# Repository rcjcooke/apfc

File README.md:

# apfc
Aeroponics Personal Food Computer

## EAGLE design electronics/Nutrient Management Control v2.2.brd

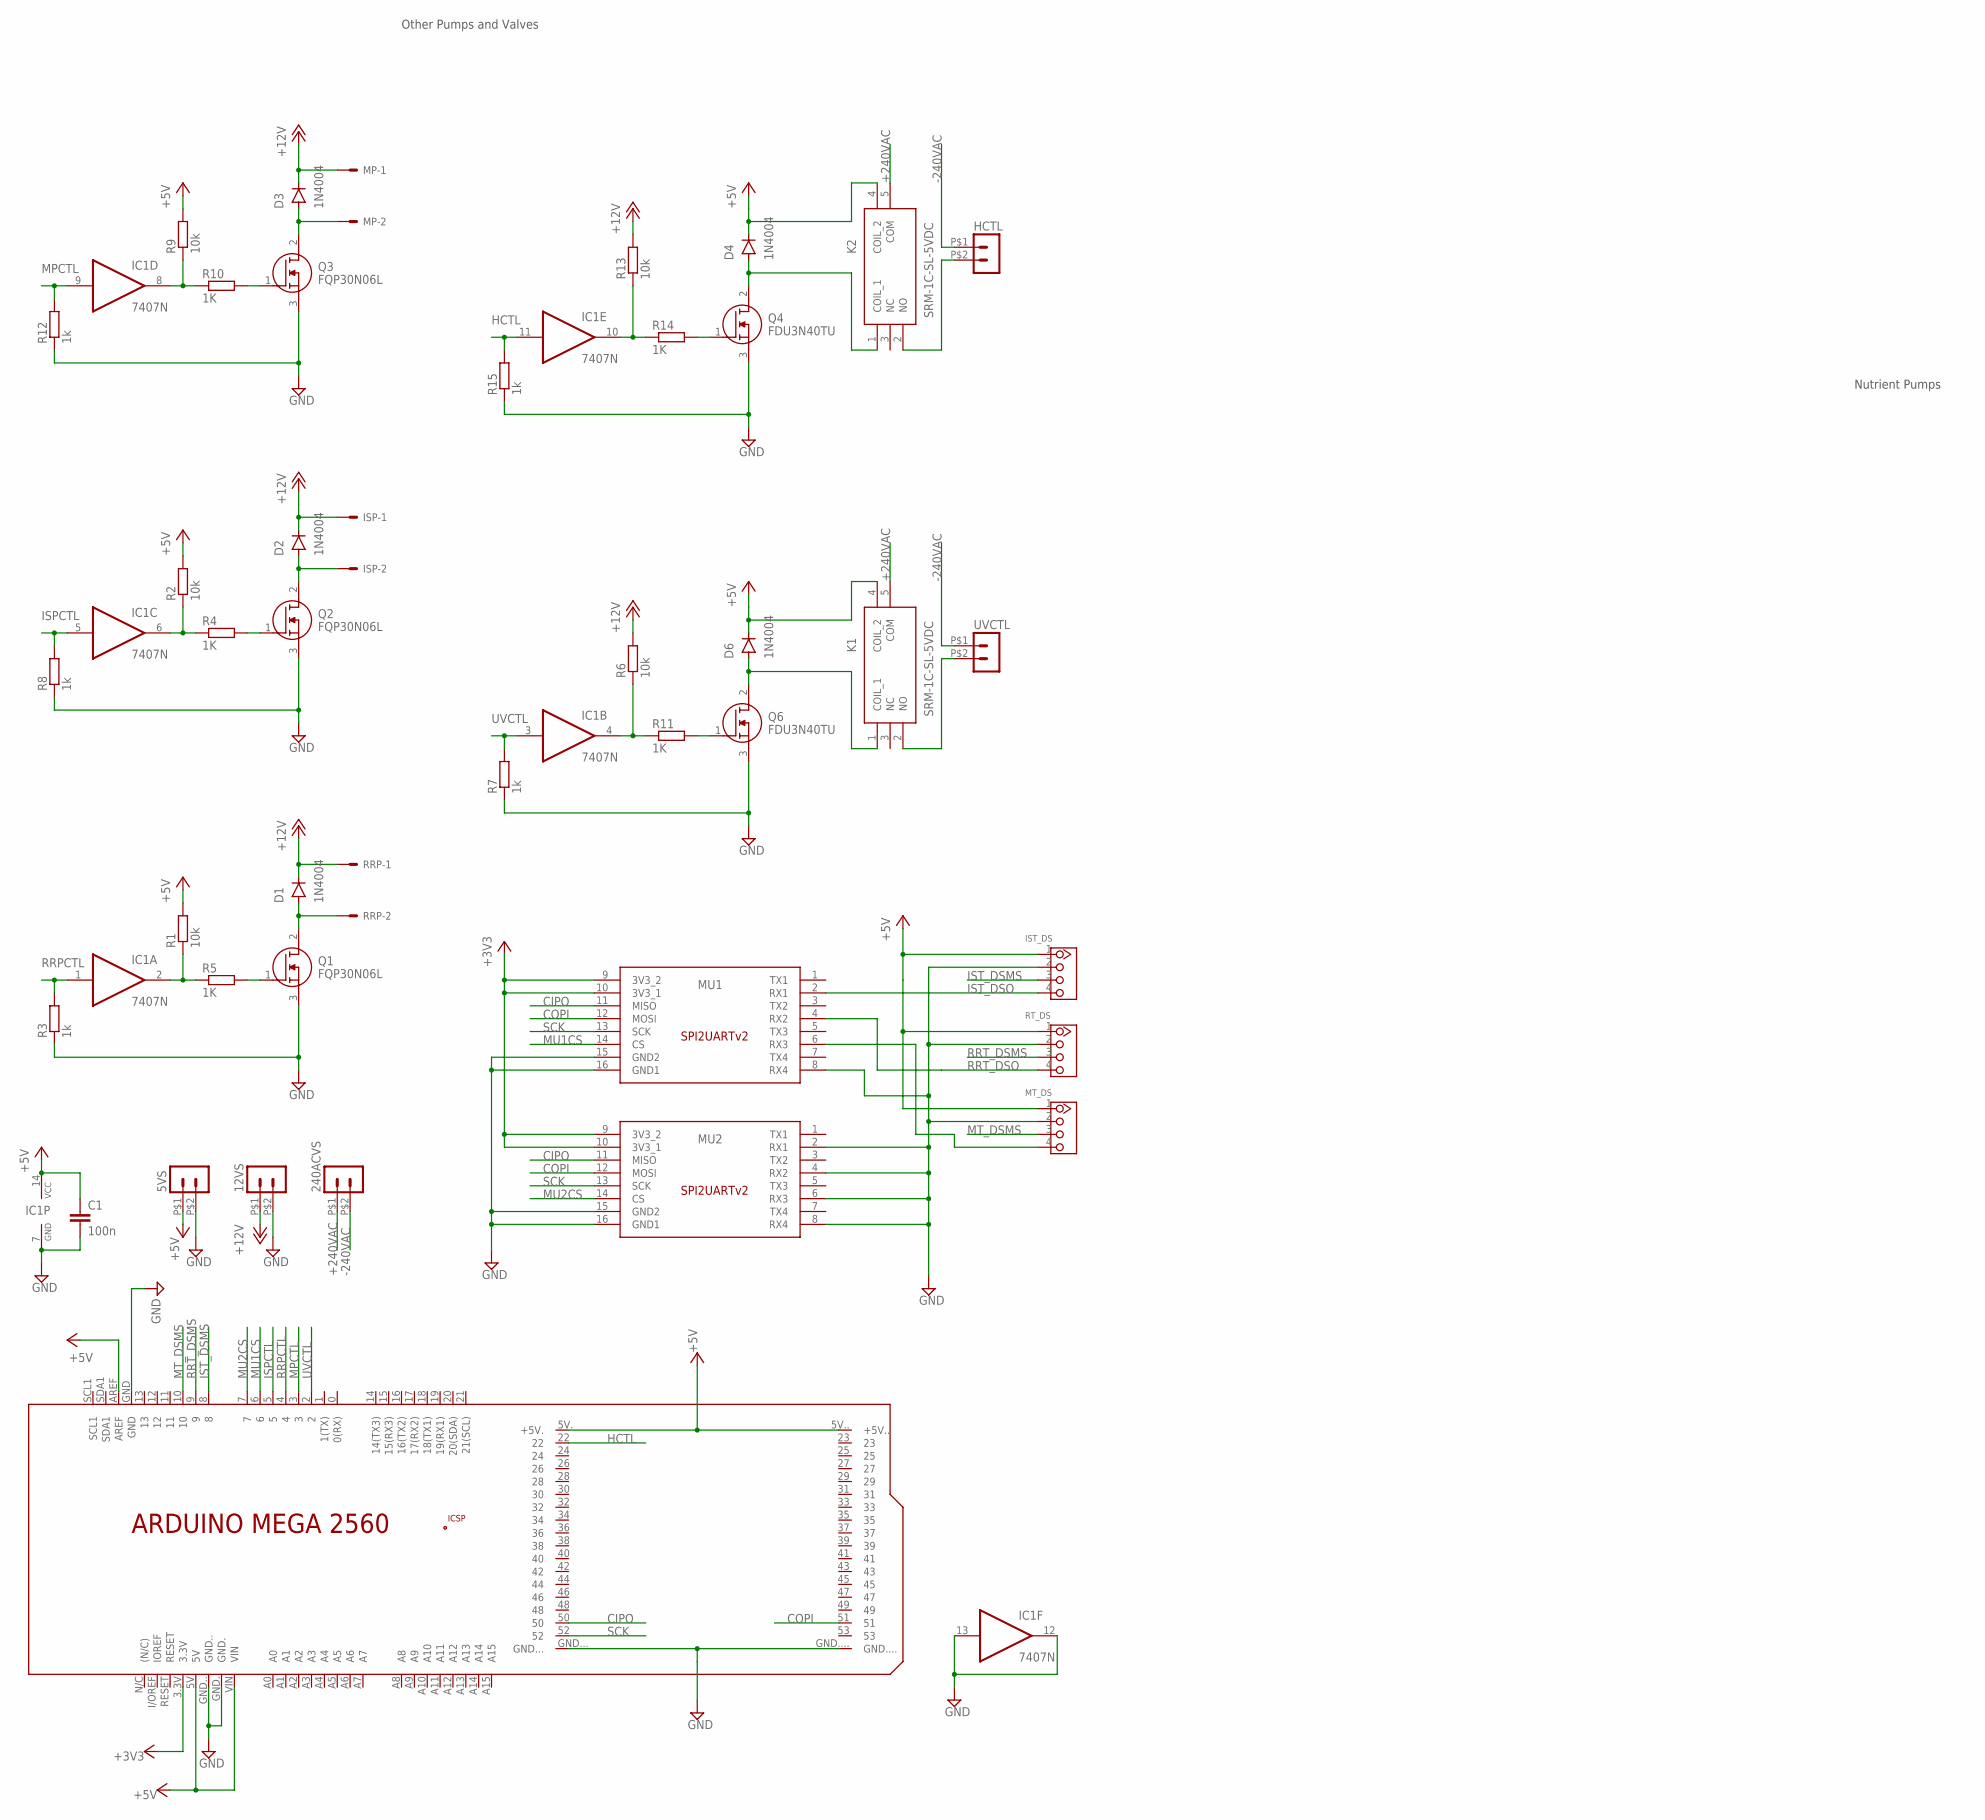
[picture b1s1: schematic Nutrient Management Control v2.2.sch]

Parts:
5VS, 12VS, 240ACVS: HEADER_POS2_43650-0215; 43650-0215
C1: 100n; C050-024X044
D1, D2, D3, D4, D6: 1N4004; DO-41
HCTL: HEADER_POS2_43650-0215; 43650-0215
IC1: 7407N; DIL14
ISP: JST-XH-02-PIN-LONG-PAD; JST-XH-02-PACKAGE-LONG-PAD
IST_DS: 4P-2.0-90D; HW4-2.0-90D
K1, K2: SRM-1C-SL-5VDC; SRM1CSL5VDC
MP: JST-XH-02-PIN-LONG-PAD; JST-XH-02-PACKAGE-LONG-PAD
MT_DS: 4P-2.0-90D; HW4-2.0-90D
MU1, MU2: SPI2UART_HEADERS; SPI2UARTV2
PCB2: ARDUINO_MEGA2560_SHIELD
Q1, Q2, Q3: FQP30N06L; TO254P470X1016X2019-3P
Q4, Q6: FDU3N40TU; TO229P250X658X985-3P
R1, R2, R6, R9, R13: 10k; 0204/7
R3, R7, R8, R12, R15: 1k; 0204/7
R4, R5, R10, R11, R14: 1K; 0204/7
RRP: JST-XH-02-PIN-LONG-PAD; JST-XH-02-PACKAGE-LONG-PAD
RT_DS: 4P-2.0-90D; HW4-2.0-90D
UVCTL: HEADER_POS2_43650-0215; 43650-0215

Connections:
+3V3: MU1.9 (3V3_2), MU1.10 (3V3_1), MU2.9 (3V3_2), MU2.10 (3V3_1), PCB2.3.3V
+5V: 5VS.P$1 (1), C1.1, D4.C, D6.C, IC1.14 (VCC), IST_DS.1, K1.4 (COIL_2), K2.4 (COIL_2), MT_DS.1, PCB2.5V, PCB2.5V. (+5V.), PCB2.5V.. (+5V..), PCB2.AREF, PCB2.VIN, R1.2, R2.2, R9.2, RT_DS.1
+12V: 12VS.P$1 (1), D1.C, D2.C, D3.C, ISP.1, MP.1, R6.2, R13.2, RRP.1
+240VAC: 240ACVS.P$1 (1), K1.5 (COM), K2.5 (COM)
-240VAC: 240ACVS.P$2 (2), HCTL.P$1 (1), UVCTL.P$1 (1)
CIPO: MU1.11 (MISO), MU2.11 (MISO), PCB2.50
COPI: MU1.12 (MOSI), MU2.12 (MOSI), PCB2.51
GND: 5VS.P$2 (2), 12VS.P$2 (2), C1.2, IC1.7 (GND), IC1.12 (O), IC1.13 (I), IST_DS.2, MT_DS.2, MU1.8 (RX4), MU1.15 (GND2), MU1.16 (GND1), MU2.2 (RX1), MU2.4 (RX2), MU2.6 (RX3), MU2.8 (RX4), MU2.15 (GND2), MU2.16 (GND1), PCB2.GND, PCB2.GND., PCB2.GND.., PCB2.GND..., PCB2.GND...., Q1.3 (S), Q2.3 (S), Q3.3 (S), Q4.3 (S), Q6.3 (S), R3.1, R7.1, R8.1, R12.1, R15.1, RT_DS.2
HCTL: IC1.11 (I), PCB2.22, R15.2
ISPCTL: IC1.5 (I), PCB2.5, R8.2
IST_DSMS: IST_DS.3, PCB2.8
IST_DSO: IST_DS.4, MU1.2 (RX1)
MPCTL: IC1.9 (I), PCB2.3, R12.2
MT_DSMS: MT_DS.3, PCB2.10
MU1CS: MU1.14 (CS), PCB2.6
MU2CS: MU2.14 (CS), PCB2.7
unnamed: D2.A, ISP.2, Q2.2 (D)
unnamed: IC1.6 (O), R2.1, R4.1
unnamed: IC1.2 (O), R1.1, R5.1
unnamed: Q2.1 (G), R4.2
unnamed: Q1.1 (G), R5.2
unnamed: D3.A, MP.2, Q3.2 (D)
unnamed: K1.2 (NO), UVCTL.P$2 (2)
unnamed: IC1.8 (O), R9.1, R10.1
unnamed: Q3.1 (G), R10.2
unnamed: D1.A, Q1.2 (D), RRP.2
unnamed: MT_DS.4, MU1.6 (RX3)
unnamed: D4.A, K2.1 (COIL_1), Q4.2 (D)
unnamed: Q6.1 (G), R11.2
unnamed: HCTL.P$2 (2), K2.2 (NO)
unnamed: Q4.1 (G), R14.2
unnamed: IC1.10 (O), R13.1, R14.1
unnamed: IC1.4 (O), R6.1, R11.1
unnamed: D6.A, K1.1 (COIL_1), Q6.2 (D)
RRPCTL: IC1.1 (I), PCB2.4, R3.2
RRT_DSMS: PCB2.9, RT_DS.3
RRT_DSO: MU1.4 (RX2), RT_DS.4
SCK: MU1.13 (SCK), MU2.13 (SCK), PCB2.52
UVCTL: IC1.3 (I), PCB2.2, R7.2

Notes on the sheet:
Nutrient Pumps
Other Pumps and Valves

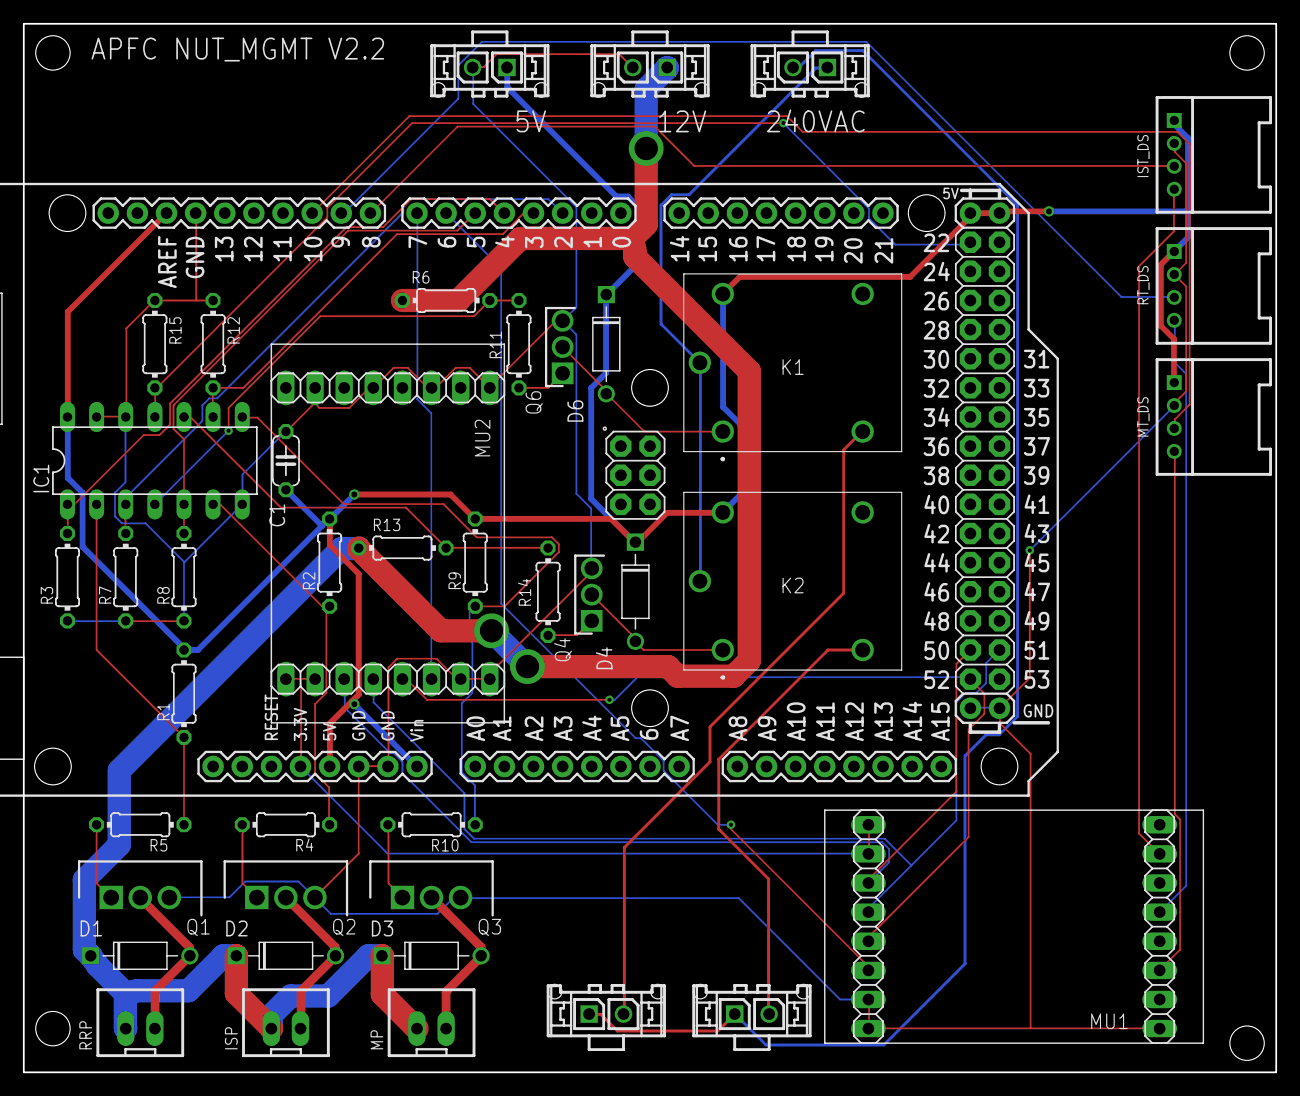
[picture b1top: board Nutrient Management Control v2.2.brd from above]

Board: 2 copper layers, 109.2 x 91.4 mm, 43 parts (0 on the bottom side), 39 nets.

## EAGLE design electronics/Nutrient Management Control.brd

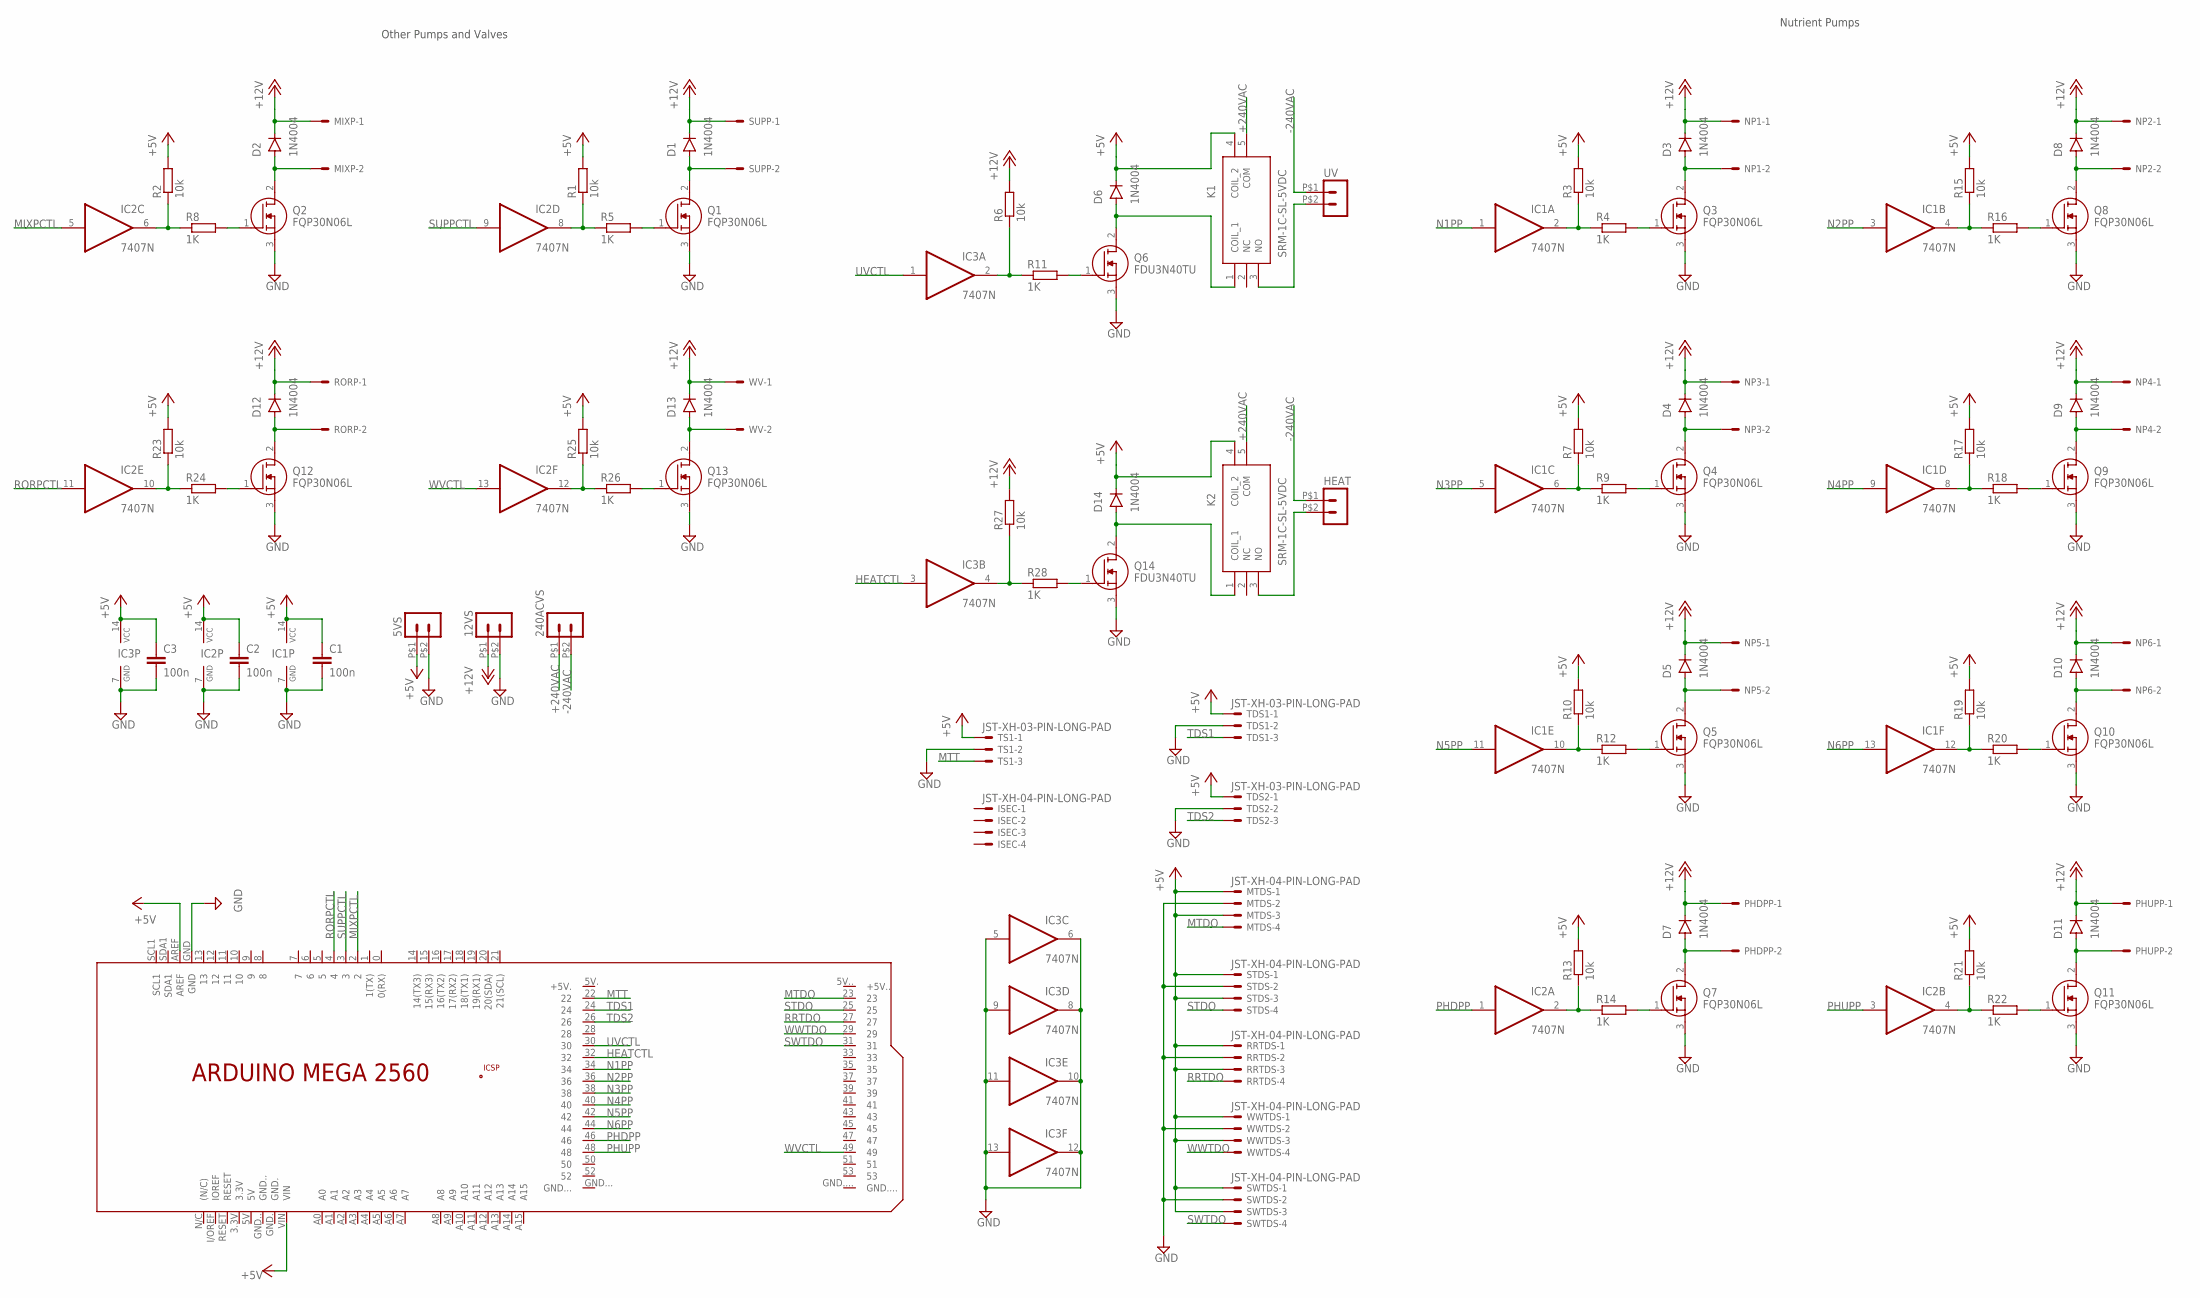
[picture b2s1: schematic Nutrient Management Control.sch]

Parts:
5VS, 12VS, 240ACVS: HEADER_POS2_43650-0215; 43650-0215
C1, C2, C3: 100n; C050-024X044
D1, D2, D3, D4, D5, D6, D7, D8, D9, D10, D11, D12, D13, D14: 1N4004; DO-41
HEAT: HEADER_POS2_43650-0215; 43650-0215
IC1, IC2, IC3: 7407N; DIL14
ISEC: JST-XH-04-PIN-LONG-PAD; JST-XH-04-PACKAGE-LONG-PAD
K1, K2: SRM-1C-SL-5VDC; SRM1CSL5VDC
MIXP: JST-XH-02-PIN-LONG-PAD; JST-XH-02-PACKAGE-LONG-PAD
MTDS: JST-XH-04-PIN-LONG-PAD; JST-XH-04-PACKAGE-LONG-PAD
NP1, NP2, NP3, NP4, NP5, NP6: JST-XH-02-PIN-LONG-PAD; JST-XH-02-PACKAGE-LONG-PAD
PCB2: ARDUINO_MEGA2560_SHIELD
PHDPP: JST-XH-02-PIN-LONG-PAD; JST-XH-02-PACKAGE-LONG-PAD
PHUPP: JST-XH-02-PIN-LONG-PAD; JST-XH-02-PACKAGE-LONG-PAD
Q1, Q2, Q3, Q4, Q5, Q7, Q8, Q9, Q10, Q11, Q12, Q13: FQP30N06L; TO254P470X1016X2019-3P
Q6, Q14: FDU3N40TU; TO229P250X658X985-3P
R1, R2, R3, R6, R7, R10, R13, R15, R17, R19, R21, R23, R25, R27: 10k; 0204/7
R4, R5, R8, R9, R11, R12, R14, R16, R18, R20, R22, R24, R26, R28: 1K; 0204/7
RORP: JST-XH-02-PIN-LONG-PAD; JST-XH-02-PACKAGE-LONG-PAD
RRTDS: JST-XH-04-PIN-LONG-PAD; JST-XH-04-PACKAGE-LONG-PAD
STDS: JST-XH-04-PIN-LONG-PAD; JST-XH-04-PACKAGE-LONG-PAD
SUPP: JST-XH-02-PIN-LONG-PAD; JST-XH-02-PACKAGE-LONG-PAD
SWTDS: JST-XH-04-PIN-LONG-PAD; JST-XH-04-PACKAGE-LONG-PAD
TDS1, TDS2: JST-XH-03-PIN-LONG-PAD; JST-XH-03-PACKAGE-LONG-PAD
TS1: JST-XH-03-PIN-LONG-PAD; JST-XH-03-PACKAGE-LONG-PAD
UV: HEADER_POS2_43650-0215; 43650-0215
WV: JST-XH-02-PIN-LONG-PAD; JST-XH-02-PACKAGE-LONG-PAD
WWTDS: JST-XH-04-PIN-LONG-PAD; JST-XH-04-PACKAGE-LONG-PAD

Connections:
+5V: 5VS.P$1 (1), C1.1, C2.1, C3.1, D6.C, D14.C, IC1.14 (VCC), IC2.14 (VCC), IC3.14 (VCC), K1.4 (COIL_2), K2.4 (COIL_2), MTDS.1, MTDS.3, PCB2.AREF, PCB2.VIN, R1.2, R2.2, R3.2, R7.2, R10.2, R13.2, R15.2, R17.2, R19.2, R21.2, R23.2, R25.2, RRTDS.1, RRTDS.3, STDS.1, STDS.3, SWTDS.1, SWTDS.3, TDS1.1, TDS2.1, TS1.1, WWTDS.1, WWTDS.3
+12V: 12VS.P$1 (1), D1.C, D2.C, D3.C, D4.C, D5.C, D7.C, D8.C, D9.C, D10.C, D11.C, D12.C, D13.C, MIXP.1, NP1.1, NP2.1, NP3.1, NP4.1, NP5.1, NP6.1, PHDPP.1, PHUPP.1, R6.2, R27.2, RORP.1, SUPP.1, WV.1
+240VAC: 240ACVS.P$1 (1), K1.5 (COM), K2.5 (COM)
-240VAC: 240ACVS.P$2 (2), HEAT.P$1 (1), UV.P$1 (1)
GND: 5VS.P$2 (2), 12VS.P$2 (2), C1.2, C2.2, C3.2, IC1.7 (GND), IC2.7 (GND), IC3.5 (I), IC3.6 (O), IC3.7 (GND), IC3.8 (O), IC3.9 (I), IC3.10 (O), IC3.11 (I), IC3.12 (O), IC3.13 (I), MTDS.2, PCB2.GND, Q1.3 (S), Q2.3 (S), Q3.3 (S), Q4.3 (S), Q5.3 (S), Q6.3 (S), Q7.3 (S), Q8.3 (S), Q9.3 (S), Q10.3 (S), Q11.3 (S), Q12.3 (S), Q13.3 (S), Q14.3 (S), RRTDS.2, STDS.2, SWTDS.2, TDS1.2, TDS2.2, TS1.2, WWTDS.2
HEATCTL: IC3.3 (I), PCB2.32
MIXPCTL: IC2.5 (I), PCB2.2
MTDO: MTDS.4, PCB2.23
MTT: PCB2.22, TS1.3
N1PP: IC1.1 (I), PCB2.34
N2PP: IC1.3 (I), PCB2.36
N3PP: IC1.5 (I), PCB2.38
N4PP: IC1.9 (I), PCB2.40
N5PP: IC1.11 (I), PCB2.42
N6PP: IC1.13 (I), PCB2.44
unnamed: D2.A, MIXP.2, Q2.2 (D)
unnamed: D3.A, NP1.2, Q3.2 (D)
unnamed: IC2.8 (O), R1.1, R5.1
unnamed: Q2.1 (G), R8.2
unnamed: Q1.1 (G), R5.2
unnamed: IC1.2 (O), R3.1, R4.1
unnamed: K1.3 (NO), UV.P$2 (2)
unnamed: Q3.1 (G), R4.2
unnamed: IC2.6 (O), R2.1, R8.1
unnamed: D1.A, Q1.2 (D), SUPP.2
unnamed: D4.A, NP3.2, Q4.2 (D)
unnamed: IC1.6 (O), R7.1, R9.1
unnamed: Q6.1 (G), R11.2
unnamed: Q4.1 (G), R9.2
unnamed: D5.A, NP5.2, Q5.2 (D)
unnamed: IC1.10 (O), R10.1, R12.1
unnamed: IC3.2 (O), R6.1, R11.1
unnamed: Q5.1 (G), R12.2
unnamed: D7.A, PHDPP.2, Q7.2 (D)
unnamed: IC2.2 (O), R13.1, R14.1
unnamed: D6.A, K1.1 (COIL_1), Q6.2 (D)
unnamed: Q7.1 (G), R14.2
unnamed: D8.A, NP2.2, Q8.2 (D)
unnamed: IC1.4 (O), R15.1, R16.1
unnamed: Q8.1 (G), R16.2
unnamed: D9.A, NP4.2, Q9.2 (D)
unnamed: IC1.8 (O), R17.1, R18.1
unnamed: Q9.1 (G), R18.2
unnamed: D10.A, NP6.2, Q10.2 (D)
unnamed: IC1.12 (O), R19.1, R20.1
unnamed: Q10.1 (G), R20.2
unnamed: D11.A, PHUPP.2, Q11.2 (D)
unnamed: IC2.4 (O), R21.1, R22.1
unnamed: Q11.1 (G), R22.2
unnamed: D12.A, Q12.2 (D), RORP.2
unnamed: IC2.10 (O), R23.1, R24.1
unnamed: Q12.1 (G), R24.2
unnamed: D13.A, Q13.2 (D), WV.2
unnamed: IC2.12 (O), R25.1, R26.1
unnamed: Q13.1 (G), R26.2
unnamed: D14.A, K2.1 (COIL_1), Q14.2 (D)
unnamed: HEAT.P$2 (2), K2.3 (NO)
unnamed: Q14.1 (G), R28.2
unnamed: IC3.4 (O), R27.1, R28.1
PHDPP: IC2.1 (I), PCB2.46
PHUPP: IC2.3 (I), PCB2.48
RORPCTL: IC2.11 (I), PCB2.4
RRTDO: PCB2.27, RRTDS.4
STDO: PCB2.25, STDS.4
SUPPCTL: IC2.9 (I), PCB2.3
SWTDO: PCB2.31, SWTDS.4
TDS1: PCB2.24, TDS1.3
TDS2: PCB2.26, TDS2.3
UVCTL: IC3.1 (I), PCB2.30
WVCTL: IC2.13 (I), PCB2.49
WWTDO: PCB2.29, WWTDS.4

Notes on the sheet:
Nutrient Pumps
Other Pumps and Valves

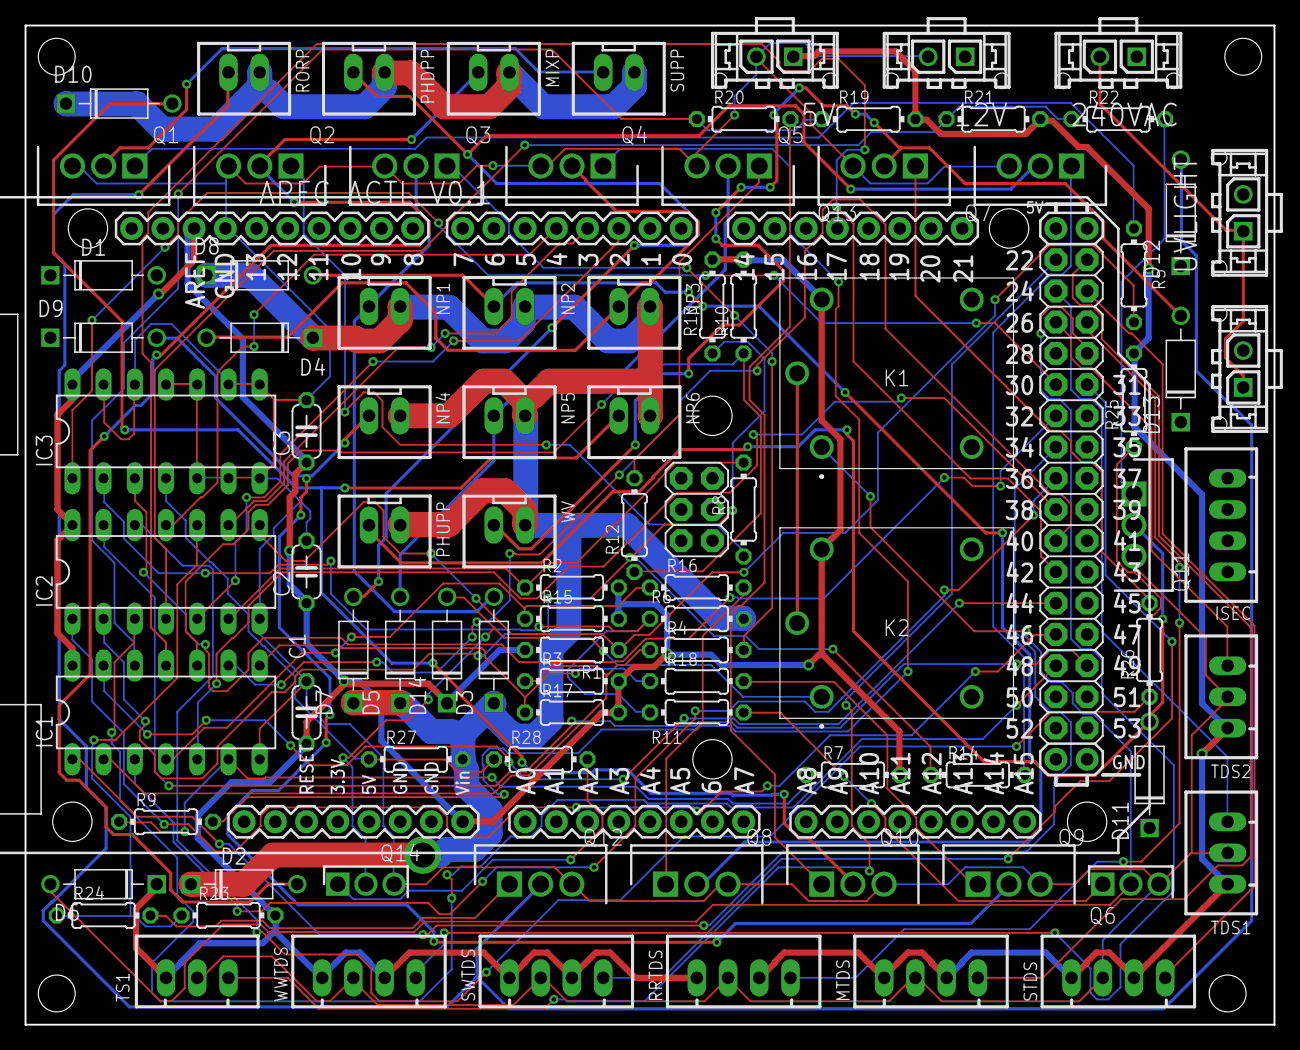
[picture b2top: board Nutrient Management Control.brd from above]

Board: 2 copper layers, 101.6 x 81.3 mm, 91 parts (0 on the bottom side), 71 nets.

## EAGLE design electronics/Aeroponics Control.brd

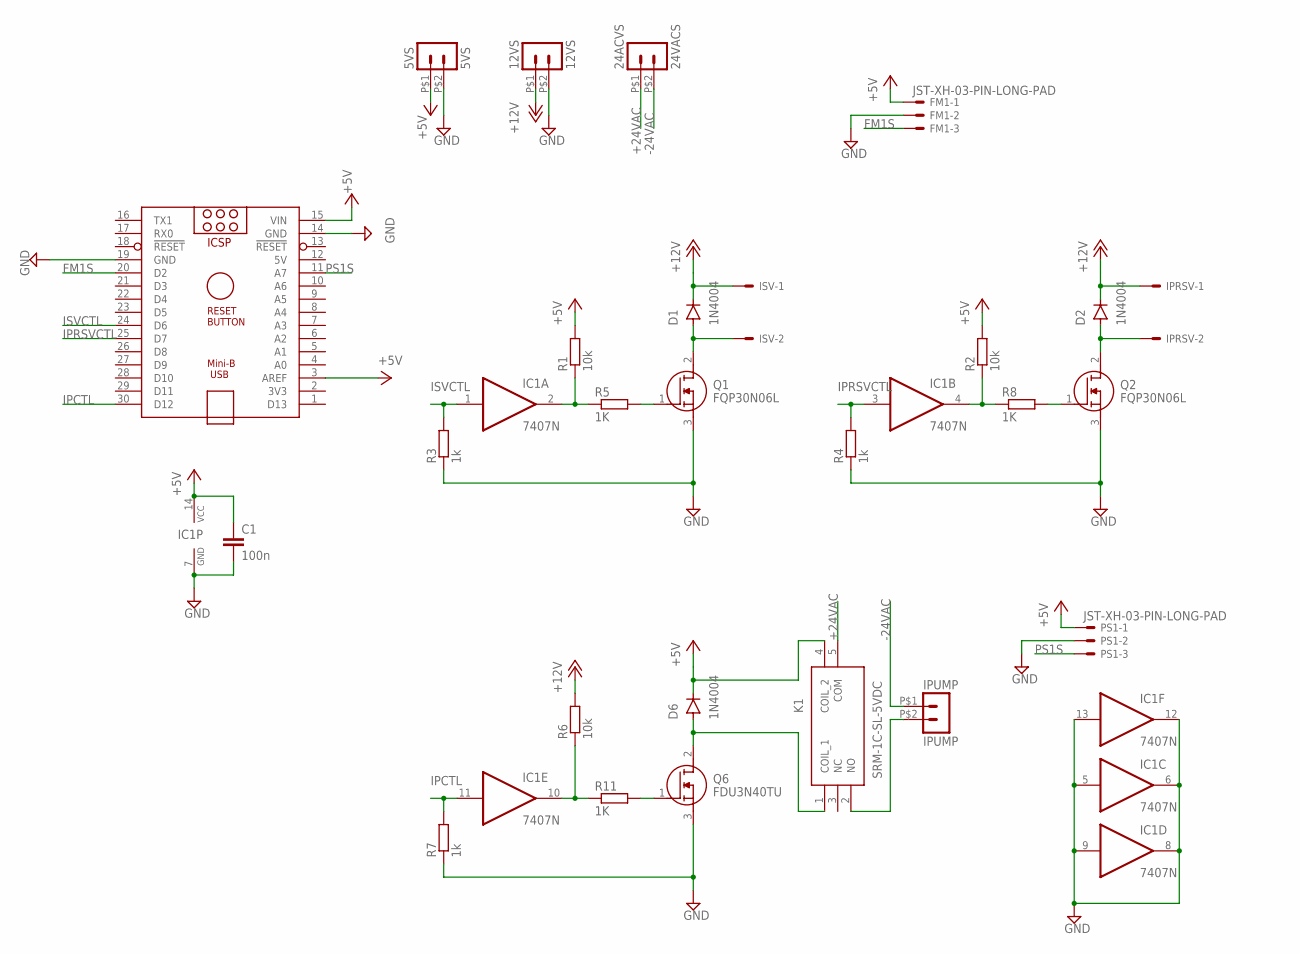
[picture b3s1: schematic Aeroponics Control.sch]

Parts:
5VS: 5VS; 43650-0215
12VS: 12VS; 43650-0215
24ACVS: 24VACS; 43650-0215
C1: 100n; C050-024X044
D1, D2, D6: 1N4004; DO-41
FM1: JST-XH-03-PIN-LONG-PAD; JST-XH-03-PACKAGE-LONG-PAD
IC1: 7407N; DIL14
IPRSV: JST-XH-02-PIN-LONG-PAD; JST-XH-02-PACKAGE-LONG-PAD
IPUMP: IPUMP; 43650-0215
ISV: JST-XH-02-PIN-LONG-PAD; JST-XH-02-PACKAGE-LONG-PAD
K1: SRM-1C-SL-5VDC; SRM1CSL5VDC
PCB1: ARDUINO_NANOARDUINO_NANO_HEADERS; ARDUINO_NANO
PS1: JST-XH-03-PIN-LONG-PAD; JST-XH-03-PACKAGE-LONG-PAD
Q1, Q2: FQP30N06L; TO254P470X1016X2019-3P
Q6: FDU3N40TU; TO229P250X658X985-3P
R1, R2, R6: 10k; 0204/7
R3, R4, R7: 1k; 0204/7
R5, R8, R11: 1K; 0204/7

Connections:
5V: PCB1.12 (5V)
+5V: 5VS.P$1 (1), C1.1, D6.C, FM1.1, IC1.14 (VCC), K1.4 (COIL_2), PCB1.3 (AREF), PCB1.15 (VIN), PS1.1, R1.2, R2.2
+12V: 12VS.P$1 (1), D1.C, D2.C, IPRSV.1, ISV.1, R6.2
+24VAC: 24ACVS.P$1 (1), K1.5 (COM)
-24VAC: 24ACVS.P$2 (2), IPUMP.P$1 (1)
FM1S: FM1.3, PCB1.20 (D2)
GND: 5VS.P$2 (2), 12VS.P$2 (2), C1.2, FM1.2, IC1.5 (I), IC1.6 (O), IC1.7 (GND), IC1.8 (O), IC1.9 (I), IC1.12 (O), IC1.13 (I), PCB1.14 (GND), PCB1.19 (GND), PS1.2, Q1.3 (S), Q2.3 (S), Q6.3 (S), R3.1, R4.1, R7.1
IPCTL: IC1.11 (I), PCB1.30 (D12), R7.2
IPRSVCTL: IC1.3 (I), PCB1.25 (D7), R4.2
ISVCTL: IC1.1 (I), PCB1.24 (D6), R3.2
unnamed: D2.A, IPRSV.2, Q2.2 (D)
unnamed: IC1.2 (O), R1.1, R5.1
unnamed: Q2.1 (G), R8.2
unnamed: Q1.1 (G), R5.2
unnamed: IPUMP.P$2 (2), K1.2 (NO)
unnamed: IC1.4 (O), R2.1, R8.1
unnamed: D1.A, ISV.2, Q1.2 (D)
unnamed: Q6.1 (G), R11.2
unnamed: IC1.10 (O), R6.1, R11.1
unnamed: D6.A, K1.1 (COIL_1), Q6.2 (D)
PS1S: PCB1.11 (A7), PS1.3

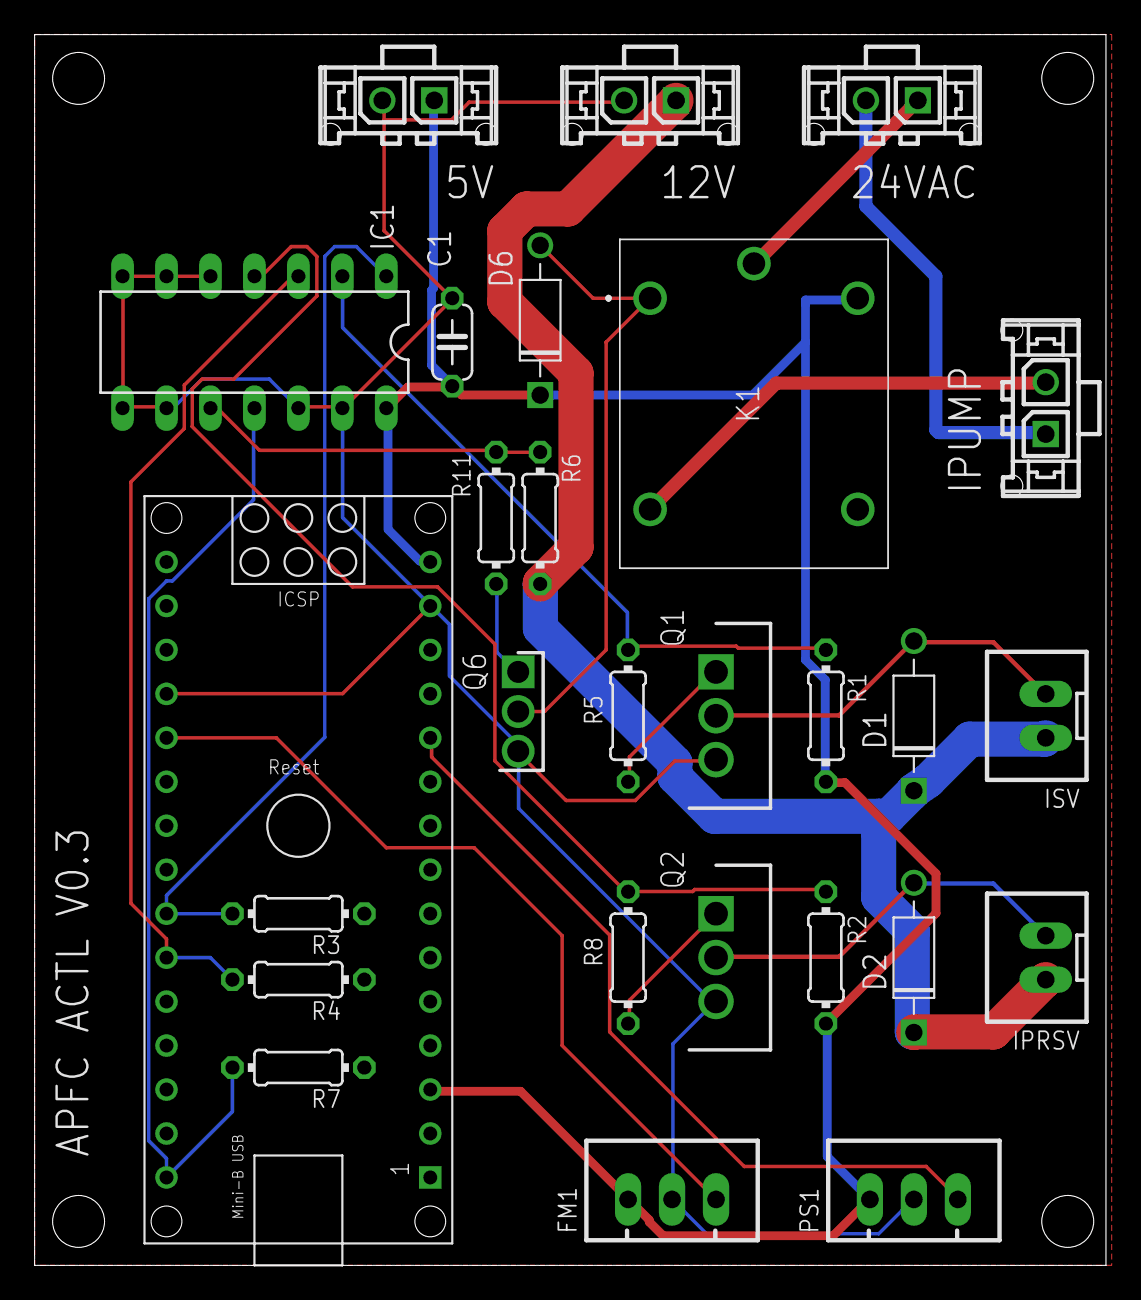
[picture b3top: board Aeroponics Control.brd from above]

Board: 2 copper layers, 61.9 x 71.1 mm, 27 parts (0 on the bottom side), 20 nets.

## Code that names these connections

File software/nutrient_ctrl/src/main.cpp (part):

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 * Constants
 ************************/
// MultiUART Board 2 Chip Select pin
static const uint8_t MU2CS = 7;
// MultiUART Board 1 Chip Select pin
static const uint8_t MU1CS = 6;

// Irrigation Supply Pump control pin
static const uint8_t ISPCTL = 5;
// Runoff Recycling Pump control pin
static const uint8_t RRPCTL = 4;
// Mixing Pump control pin
static const uint8_t MPCTL = 3;

// UV Sterilisation Control pin
static const uint8_t UVCTL = 2;
// Heater Control pin
static const uint8_t HCTL = 22;
// Water Filter System Flush Solenoid Control pin
static const uint8_t WSFCTL = 23;

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static const char WWT_MUART_INDEX = 1;

// Mixing Tank Depth Sensor: Processed Value/Real-time Value Output Selection pin
static const uint8_t MT_DSMS = 10;
// Runoff Recycling Tank Depth Sensor: Processed Value/Real-time Value Output Selection pin
static const uint8_t RRT_DSMS = 9;
// Irrigation Supply Tank Depth Sensor: Processed Value/Real-time Value Output Selection pin
static const uint8_t IST_DSMS = 8;
// Water Supply Tank Depth Sensor: Processed Value/Real-time Value Output Selection pin
static const uint8_t WST_DSMS = 11;
// Waste Water Tank Depth Sensor: Processed Value/Real-time Value Output Selection pin
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
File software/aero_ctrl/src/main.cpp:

#include <Arduino.h>

#include <SerialDebugger.hpp>

#include "SprayController.hpp"
#include "FlowSensor.hpp"
#include "IrrigationPressureController.hpp"

// If true, serial output from the Arduino is in human readable form - this means comms with the Raspberry Pi controller won't work
#define DEBUG_SOLO true

/************************
 * Constants
 ************************/
// Irrigation solenoid valve control pin
static const uint8_t ISVCTL = 6;
// Irrigation pressure release solenoid valve control pin
static const uint8_t IPRSVCTL = 7;
// Irrigation Compressor Control pin
static const uint8_t IPCTL = 12;
// Flowrate Meter Signal - PWM: F=(38*Q), Q=L / min
static const uint8_t FM1S = 2;
// Pressure Sensor Signal - Analogue: 0-5VDC range
static const uint8_t PS1S = A7;

// The total number of alarm generators
static const int NUM_ALARM_GENERATORS = 1;

// Debug keys
static const String DEBUG_COMPRESSOR_ON_KEY = "Compressor on";

/************************
 * Variables
 ************************/

// Irrigation spray controller
SprayController* gSprayController;
// Irrigation spray flow sensor
FlowSensor* gFlowSensor;
// Irrigation pressure controller
IrrigationPressureController* gIrrigationPressureController;

// The array of all alarm generators
AlarmGenerator** gAGs;
// The serial debug interface (show values and allow control)
SerialDebugger* mDebugger;

// Last spray volume / millilitres
double gLastSprayVolumeMl = 0;

/*********************
 * Utility functions
 *********************/
// Creates a human readable alarm string used for debug
String createAlarmString(int numAGs, AlarmGenerator** ags) {
	String alarmString = "";
	for (int agi = 0; agi < numAGs; agi++) {
		AlarmGenerator* ag = ags[agi];
		bool* aStates = ag->getAlarmStates();
		int numAlarmCodes = ag->getNumAlarmCodes();
		char agCode = ag->getUniqueAlarmGeneratorCode();
		for (int i = 0; i < numAlarmCodes; i++) {
			if (aStates[i]) {
				if (alarmString.length() != 0) alarmString += ',';
				alarmString += agCode;
				alarmString += i;
			}
		}
	}
	return alarmString;
}

// Process change requests made on the debug serial interface
void processDebugValueChangesFromUser(String key, String value) {
	// At present this debug interface only supports one value being changed
	if (key.equals(DEBUG_COMPRESSOR_ON_KEY)) {
		if (value.equals("1")) {
			gIrrigationPressureController->turnOnIrrigationCompressor();
		} else if (value.equals("0")) {
			gIrrigationPressureController->turnOffIrrigationCompressor();
		}
	}
}

/*********************
 * Entry point methods
 *********************/
void setup() {

	if (DEBUG_SOLO) {
		// Note: this also starts the serial interface at a baud rate of 115200 bps
		mDebugger = new SerialDebugger(115200);
		mDebugger->onValueChanged(processDebugValueChangesFromUser);
	} else {
		// TODO: Sort out serial comms interface
		Serial.begin(115200);
		// Wait for initialisation of the serial interface
		while(!Serial);
	}

  gIrrigationPressureController = new IrrigationPressureController(PS1S, IPRSVCTL, IPCTL);
	gSprayController = new SprayController(ISVCTL);
  gFlowSensor = new FlowSensor(FM1S);
  
  gSprayController->onSprayStop([]() {
    gLastSprayVolumeMl = gFlowSensor->getCumulativeVolumeMl();
    gFlowSensor->resetCumulativeVolume();
  });

	// Record which controllers are alarm generators for future access
	gAGs = new AlarmGenerator*[NUM_ALARM_GENERATORS] {gIrrigationPressureController};

}

/*
	• Spray (X = 3-5 minutes, Y = 1-5 seconds)
		○ Every X seconds, turn on spray
		○ After Y seconds, turn off spray
	• Flow measurement
		○ Every loop, record pulse count and calculate and record flow
		○ If (started spraying) record pulse count
		○ if (spraying) update current spray cumulative volume
		○ If (stopped spraying) record pulse count and reset. Replace last spray cumulative volume with current spray cumulative volume
	• Pressure management
		○ Every loop, calculate and record current pressure
		○ If (pressure < 80 PSI), turn off ap drain valve, turn on pump
		○ If (pressure > 100 PSI), turn off pump
		○ If (pressure > A1 PSI), raise alert and turn on ap drain valve
	• Controller comms
		○ Every loop, read USB serial input for:
			§ Control values for X and Y, persist to EEPROM if received
			§ Alert clear signals, clear relevant alerts if received
		○ Every second (?), send back over USB serial connection:
			§ Current flow rate
			§ Last spray volume
			§ current pressure, 
			§ Alerts,
			§ Current tank depths
			§ Pump states
			§ Valve states
      § UV light state
*/
void loop() {

  unsigned long startOfControlLoopMillis = millis();
	static unsigned long controlLoopDurationMillis = 0;

  // Spray control
  gSprayController->controlLoop();
  // Flow sensing
  gFlowSensor->controlLoop();
  // Pressure management
	gIrrigationPressureController->controlLoop();

  // Communicate any updates needed
	if (DEBUG_SOLO) {

		String currentAlarms = createAlarmString(NUM_ALARM_GENERATORS, gAGs);
		unsigned long nextSpraySecs = gSprayController->getNextSprayCountdownMillis()/1000;

		// mDebugger->updateValue("Calibration point 1 ADC value / bits", ps->getCalibationPoint1()[0]);
		// mDebugger->updateValue("Calibration point 1 pressure / PSI", ps->getCalibationPoint1()[1]);
		// mDebugger->updateValue("Calibration point 2 ADC value / bits", ps->getCalibationPoint2()[0]);
		// mDebugger->updateValue("Calibration point 2 pressure / PSI", ps->getCalibationPoint2()[1]);
		// mDebugger->updateValue("Raw pressure sensor ADC value / bits", ps->getLastRawADCValue());
		mDebugger->updateValue("Alarms", currentAlarms);
		mDebugger->updateValue("Current calculated irrigation pressure / PSI", (float) gIrrigationPressureController->getPressurePSI());
		mDebugger->updateValue("Spray Valve open", gSprayController->isValveOpen());
		mDebugger->updateValue("Drain valve open", gIrrigationPressureController->isDrainValveOpen());
		mDebugger->updateValue(DEBUG_COMPRESSOR_ON_KEY, gIrrigationPressureController->isIrrigationCompressorOn());
		mDebugger->updateValue("Flow sensor pulse count", gFlowSensor->getFlowSensorPulseCount());
		mDebugger->updateValue("Last spray volume / ml", gLastSprayVolumeMl);
		mDebugger->updateValue("Next spray in / s", nextSpraySecs);
		mDebugger->updateValue("Control loop duration / ms", (int) controlLoopDurationMillis);
		mDebugger->throttledPrintUpdate();
		mDebugger->getAndProcessUserInputUpdates();
	
	} else {
	  // TODO: Define comms protocol
	}

  controlLoopDurationMillis = millis() - startOfControlLoopMillis;

}

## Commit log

2022-08-25 Initial framework
2022-08-25 starting setup
2022-08-27 Added first couple of control flow segments
2022-08-29 Added all the controls
2022-08-29 Added some timing logs
2022-08-29 First cut of pressure sensor calibration tool
2022-09-20 Electronics tested. Added calibration and debug.
2022-09-21 Making debug more readable
2022-09-21 (Hopefully) sorted out alarms - untested as yet
2022-09-21 Fixed linking and missed scoping error
2022-09-21 Tidied into util folder
2023-04-09 Added BOM and process flow diagram
2023-04-18 Renamed Process Flow Diagram. Added some more BOM items.
2023-04-19 First upload of the Fusion 360 model
2023-04-22 Added filters to pipe inlets in case of algae
2023-04-30 Laser cutting templates and 3D printing GCode
2023-06-15 Updated aeroponics control electronics.
2023-06-16 Recut aero_ctrl to v0.2 design. Created nutrient_ctrl placeholder. Pulled out initial shared libraries.
2023-06-16 Renamed for consistency
2023-06-16 Updated logo to include lens
2023-06-18 Picked out components for nutrient management
2023-06-18 Just Microcontroller and control signals left todo
2023-06-21 First cut of Nutrient Management electronics
2023-08-06 Added as reference for crimping
2023-08-25 Post RO test changes
2023-08-26 Prevent buffer overflow. More debug.
2023-08-26 Added double type.
2023-08-26 Added get countdown to next spray
2023-08-26 Added unsigned long type
2023-08-26 Added more useful info to debug
2023-08-26 Added pull down resistors to Arduino output pins
2023-08-27 Added PRV return check valve
2023-08-28 Added TDS sensor for post RO filter
2024-09-25 Comment typo
2024-09-25 8695xzbdw: Fix for flush valve opening on microcontroller reset
2024-09-26 First cut of SerialDebuggerInput
2024-09-26 Updated for library editing
2024-09-26 Integrated new SerialDebuggerInput and renamed irrigation pump to compressor
2024-09-26 Fixed some bugs. Pulled throttling out to its own function.
2024-09-26 Updated to use new throttling method of debugger
2024-09-27 Fixed relay library component pin mapping NC and NO pins
2024-09-27 Fixed FMS1 pin assignment on Nano. Incorpated fixed Relay library component.
2024-09-27 Library update
2024-09-27 Added ability to put the raw flow sensor pulse count on the debug interface
2024-09-27 Removed Eagle autorouting backup files from version control
2024-09-27 Rolled back to sensible default spray intervals now debug isn't required
2024-10-03 Lowered pressure upper bound to adjust for compressor capability.
2024-10-03 Future notes for water supply controller
2024-10-03 Moved to shared library
2024-10-03 First cut of the nutrient controller post 2024 project restart
2024-10-04 First cut of V2.2
2024-10-04 Added Grove connector
2024-10-04 Added v2.2 system diagram
2024-10-05 Added ability to define whether the sensor returns real-time or processed data
2024-10-05 Correcting pins, debug and naming conventions
2024-10-06 Added throttle into read method and corrected distance return types to float.
2024-10-06 Removed everything superfluous to debug
2024-10-14 Fixed bug causing Arduino resets on alarm triggering
2024-10-14 Type and value cleanups. Also fix to make sure pump is _actually_ turned off on initialisation.
2024-10-14 Consolidated User input and control functionality into SerialDebugger. And pre-empted function null pointer problem.
2024-10-14 Back to working order
2024-10-17 Added first cut of SPI2UART board on headers
2024-10-17 First cut of Nutrient Management with multi UART breakout boards
2024-10-17 cleanup
2024-10-17 Added Rowland Technologies MultiUART Arduino library
2024-10-17 Formatting / comments
2024-10-17 Updated library to use more Arduino appropriate types
2024-10-17 Added first cut of interfaces that abstract a single UART interface out of the MultiUART instance
2024-10-17 New sensor interfaces that talk via a MultiUART board
2024-10-17 Cleanup and bug fix
2024-10-23 Learnings from MULTIUART testing applied. Lots of changes. Getting depths from 2 sensors works.
2024-10-23 Cleaned up debug for next stage
2024-10-23 Added UV steriliser. Changed MULTIUART CS to correct pin 6 rather than 53.
2024-10-23 Added UV Steriliser
2024-10-23 Added continued reading of depths in emergency state loop for debug / informational purposes.
2024-11-01 Put run-off pump after filter so it pulls through the filter rather than pushes through it
2025-07-20 Cleaning up pressure_calc unused files
2025-07-20 Externalised some magic numbers
2025-07-20 Sorting out Nutrient Control Electronics
2025-07-20 Created a new front mount plate for the Water Purification
2025-07-22 Added first cut of TDS sensor class
2025-07-22 Doc typo fix
2025-07-23 intro. apfc ns. Refactored to create and use StandardController. Style fixes.
2025-07-23 First cut of Water Supply Controller - tank depth alerting only.
2025-07-23 Started TODO list for Nutrient Mixing
2025-07-23 Added first cut of onewire address finder utility
2025-07-23 Added datasheet for waterproof thermometer
2025-07-23 added first cut of address finder utility
2025-07-23 Updated output format so that it can pasted into a C constant directly
2025-07-23 Moved depth sensor reading checking to a utility function on the sensor. Filled in missing virtuals on WaterSupplyController.
2025-07-23 Added temperature sensor libraries
2025-07-23 Added water supply controller
2025-07-23 Fixed passing the sensor address across to water supply controller
2025-07-23 Added temp sensors in
2025-07-23 Added filter replacement checking and flush scheduling
2025-07-23 Cleaned up TODO list
2025-07-26 Renamed datasheet to clarify what it is
